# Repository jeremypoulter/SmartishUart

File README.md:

# SmartishUart

ESP8266/ESP32 programmer and general purpose UART to USB C board

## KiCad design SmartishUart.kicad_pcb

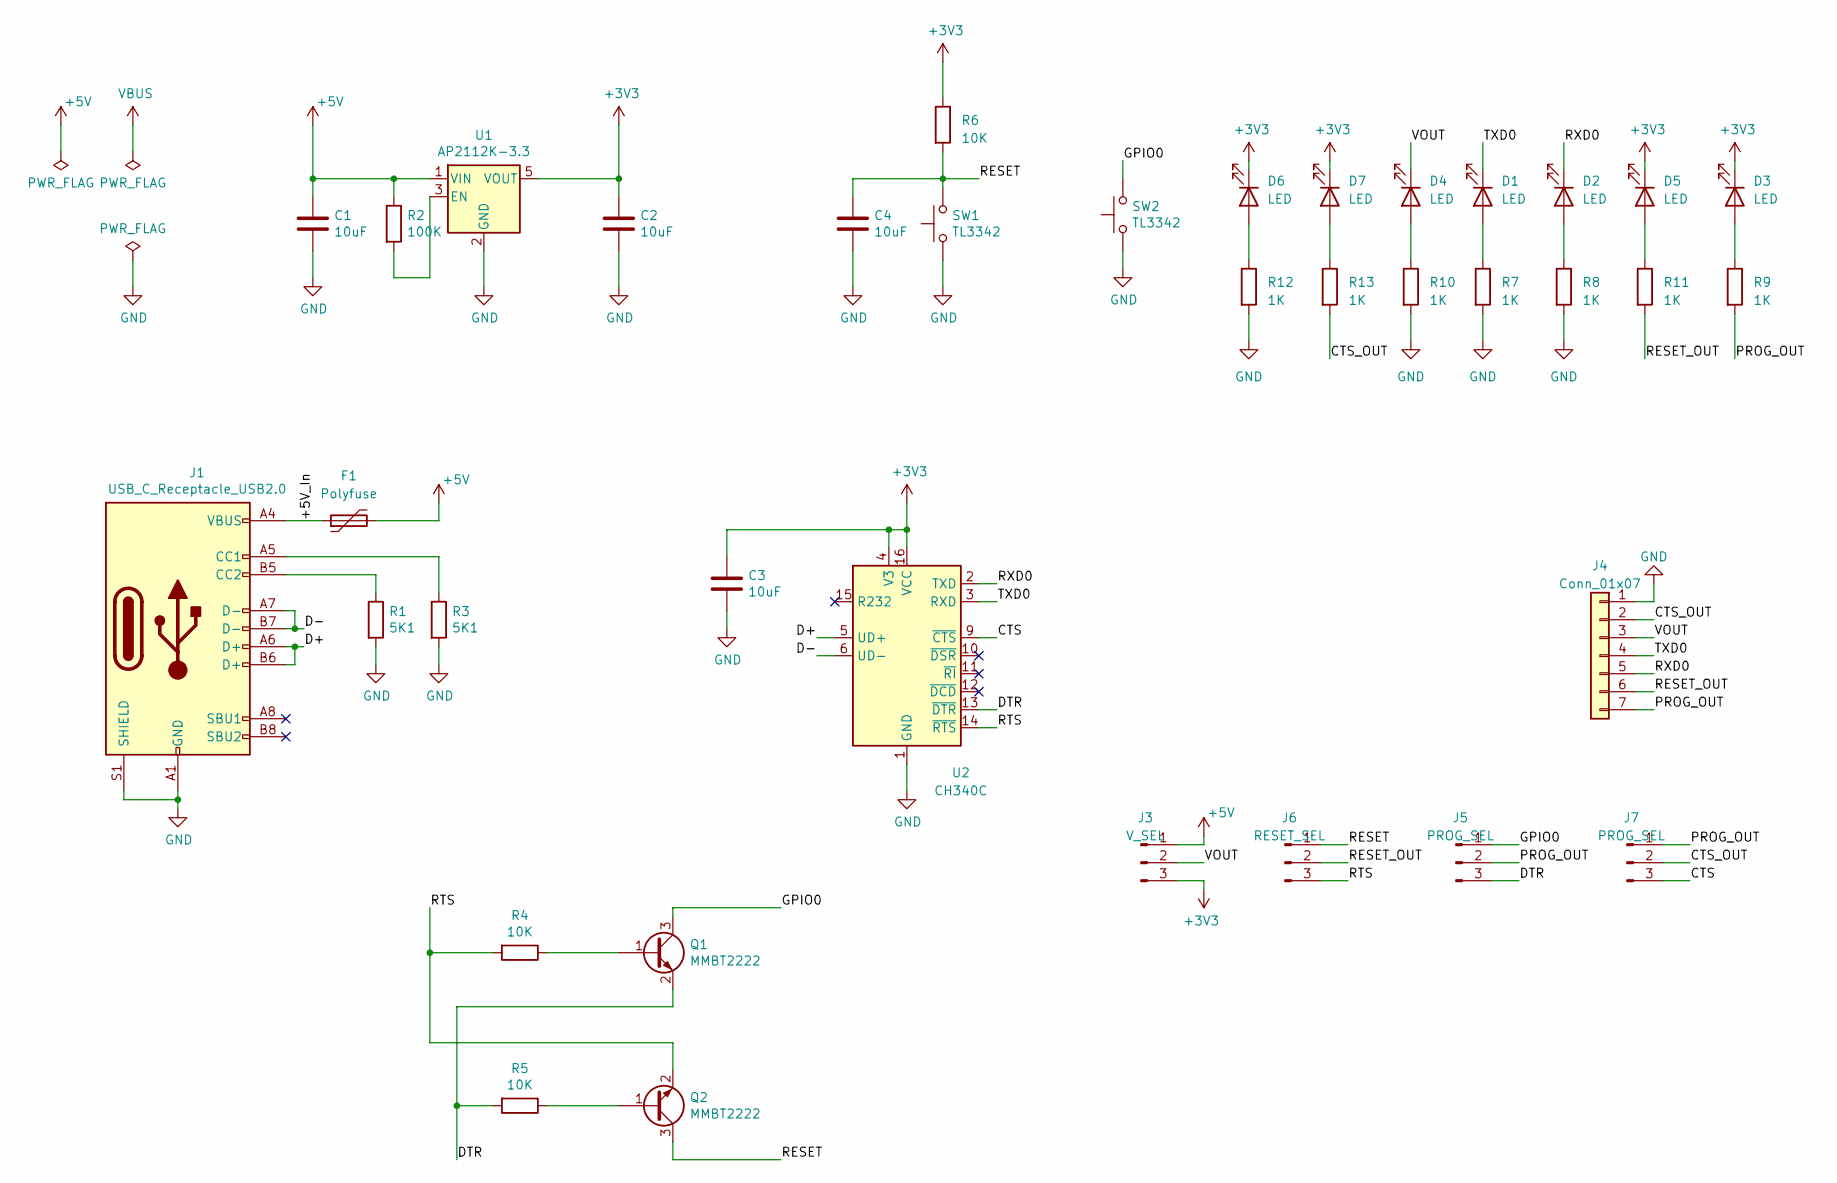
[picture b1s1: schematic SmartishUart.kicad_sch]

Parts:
C1, C2, C3, C4: 10uF; C_0805_2012Metric; LCSC C15850
D1, D2, D3, D4, D5, D6, D7: LED; LED_0805_2012Metric
F1: Polyfuse; Fuse_1206_3216Metric; LCSC C207041
J1: USB_C_Receptacle_USB2.0; USB_C_Receptacle_HRO_TYPE-C-31-M-12; LCSC C165948
J3: V_SEL; PinHeader_1x03_P2.54mm_Vertical
J4: Conn_01x07; PinHeader_1x07_P2.54mm_Vertical
J5, J7: PROG_SEL; PinHeader_1x03_P2.54mm_Vertical
J6: RESET_SEL; PinHeader_1x03_P2.54mm_Vertical
Q1, Q2: MMBT2222; SOT-23; LCSC C2891810
R1, R3: 5K1; R_0805_2012Metric; LCSC C27834
R2: 100K; R_0805_2012Metric; LCSC C149504
R4, R5: 10K; R_0805_2012Metric; LCSC C17414
R6: 10K; R_0805_2012Metric
R7, R8, R9, R10, R11, R12, R13: 1K; R_0805_2012Metric
SW1, SW2: TL3342; SW_SPST_TL3342; LCSC C318884
U1: AP2112K-3.3; SOT-23-5; LCSC C51118
U2: CH340C; SOIC-16_3.9x9.9mm_P1.27mm; LCSC C84681

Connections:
+3V3: C2.1, C3.1, D3.1 (K), D5.1 (K), D6.1 (K), D7.1 (K), J3.3, R6.1, U1.5 (VOUT), U2.4 (V3), U2.16 (VCC)
+5V: C1.1, F1.2, J3.1, R2.1, U1.1 (VIN)
/+5V_In: F1.1, J1.A4 (VBUS), J1.A9 (VBUS), J1.B4 (VBUS), J1.B9 (VBUS)
/CTS: J7.3, U2.9 (~CTS)
/CTS_OUT: J4.2, J7.2, R13.2
/D+: J1.A6 (D+), J1.B6 (D+), U2.5 (UD+)
/D-: J1.A7 (D-), J1.B7 (D-), U2.6 (UD-)
/DTR: J5.3, Q1.2 (E), R5.2, U2.13 (~DTR)
/GPIO0: J5.1, Q1.3 (C), SW2.2
/PROG_OUT: J4.7, J5.2, J7.1, R9.2
/RESET: C4.1, J6.1, Q2.3 (C), R6.2, SW1.2
/RESET_OUT: J4.6, J6.2, R11.2
/RTS: J6.3, Q2.2 (E), R4.2, U2.14 (~RTS)
/RXD0: D2.1 (K), J4.5, U2.2 (TXD)
/TXD0: D1.1 (K), J4.4, U2.3 (RXD)
/VOUT: D4.1 (K), J3.2, J4.3
GND: C1.2, C2.2, C3.2, C4.2, J1.A1 (GND), J1.A12 (GND), J1.B1 (GND), J1.B12 (GND), J1.S1 (SHIELD), J4.1, R1.2, R3.2, R7.2, R8.2, R10.2, R12.2, SW1.1, SW2.1, U1.2 (GND), U2.1 (GND)
unnamed: D1.2 (A), R7.1
unnamed: D2.2 (A), R8.1
unnamed: D3.2 (A), R9.1
unnamed: D4.2 (A), R10.1
unnamed: D5.2 (A), R11.1
unnamed: D6.2 (A), R12.1
unnamed: D7.2 (A), R13.1
unnamed: J1.A5 (CC1), R3.1
unnamed: J1.B5 (CC2), R1.1
unnamed: Q1.1 (B), R4.1
unnamed: Q2.1 (B), R5.1
unnamed: R2.2, U1.3 (EN)

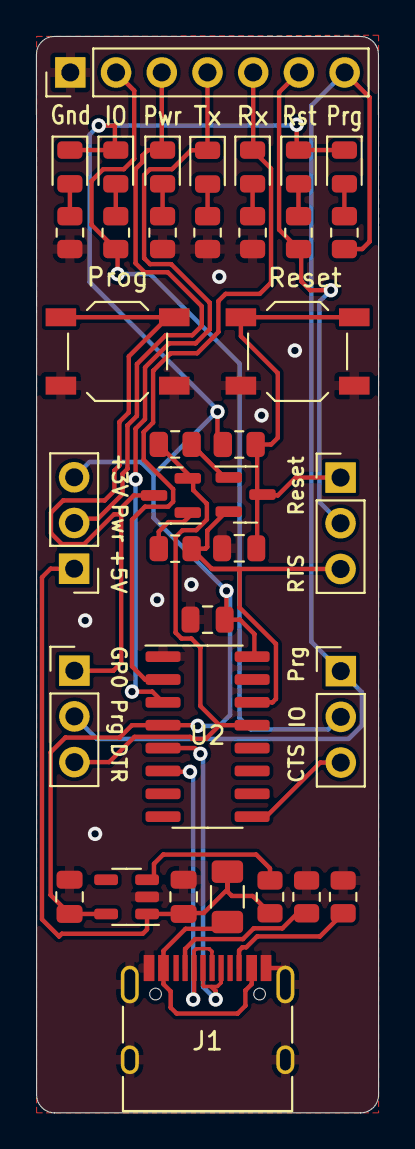
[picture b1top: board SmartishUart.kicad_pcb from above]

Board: 2 copper layers, 19.0 x 59.8 mm, 37 parts (0 on the bottom side), 29 nets.

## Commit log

2023-11-18 Various updates
    - Added LED to all output pins
    - Dropped pogopin area
    - Made 'CTS' pin configurable
    - Added lots of lables
2023-11-18 A few tweaks to the layout to make it look a little neater
2023-11-18 Use KiCAD v7 for workflow
2023-11-18 Initial laydown of tracks
2023-11-18 Fixed the USB C connector
2023-11-20 DRC error fixes
2023-11-20 Ignore Footprint warnings as we have a custom 3D model for the USB C connector
2023-11-27 Empty-Commit
2023-11-28 Fixed KiKit fabrication
2023-11-28 Updated to v7 of KiCAD
2023-11-30 Added some identification to the back of the board
